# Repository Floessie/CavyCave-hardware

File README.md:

# CavyCave (hardware)

[![CC BY-SA 4.0][cc-by-sa-shield]][cc-by-sa]

## About

*CavyCave* is a temperature controlled box for guinea pigs and other small animals kept outside in winter. This repository holds the KiCad files for the controller board.

### The box

The box is built around a dark floor tile on a base frame of battens. Walls and top cover are made of 17&nbsp;mm thick, glued spruce floorboards. The front wall is fixed with four latches and can be removed for cleaning the interior. A number of load resistors fixed with thermal glue underneath the tile provide comfortable warmth to the top, helped by a polyurethane panel, which is clamped into the base frame at the bottom.

A hole in the top right corner of the box serves together with a fan as the exhaust air outlet. To protect the cavies from inspecting the fan too closely, a two-walled plywood housing is glued onto the backside of the box corner.

Two sensors monitor the temperature and humidity: a DHT22 for air temperature and humidity located in the top right corner of the box near the fan, and a cased DS18B20 under the tile for the floor temperature.

                       | 
-----------------------------------------------------|-------------------------------------------------
 | 

### The controller board

The heart and brain of the controller board is an ATmega328P-PU as found on the popular Arduino boards. Internally supplied with 3.3&nbsp;volts it connects two DHT22 temperature and humdity sensors and two DS18B20 temperature sensors as input and drives two heating circuits and one fan. The input voltage for the board, the fan, and the heating is 5&nbsp;volts. Depending on the load resistors the heating power is about 15 to 20&nbsp;watts.

The control system can be monitored, configured and remotely controlled by an nRF24L01+.

#### BOM

Quantity | Part | Mandatory
---------|------|----------
1 | Diode 1N5817 | :heavy_check_mark:
1 | Diode 1N4001 | :heavy_check_mark:
2 | Capacitor 22pF |
5 | Capacitor 100nF | :heavy_check_mark:
1 | Capacitor 100nF |
2 | Capacitor 1µF | :heavy_check_mark:
1 | Capacitor 10µF | :heavy_check_mark:
1 | Capacitor 10µF |
1 | Capacitor 100µF | :heavy_check_mark:
1 | Resistor 100Ω | :heavy_check_mark:
1 | Resistor 100Ω |
1 | Resistor 220Ω | :heavy_check_mark:
1 | Resistor 4.7kΩ | :heavy_check_mark:
1 | Resistor 4.7kΩ |
2 | Resistor 10kΩ | :heavy_check_mark:
1 | Resistor 10kΩ |
1 | Resistor 100kΩ | :heavy_check_mark:
1 | Resistor 100kΩ |
1-6 | Resistor for LED | :heavy_check_mark:
12-18 | Load resistor 22Ω VitrOhm KH208-810B22R | :heavy_check_mark:
2m+ | Silver plated copper wire 0.8mm | :heavy_check_mark:
1 | Bicolor (3 pin, CC) or RGB (4 pin, CC) LED | :heavy_check_mark:
1 | Transistor BC337-40 | :heavy_check_mark:
1 | LDO regulator MCP1702-3002 | :heavy_check_mark:
2 | Terminal block RND 205-00232 | :heavy_check_mark:
1 | Black 4mm socket Hirschmann 930 176-100 |
1 | Red 4mm socket Hirschmann 930 176-101 |
1 | MOSFET IRLIZ34N | :heavy_check_mark:
1 | MOSFET IRLIZ34N |
1 | Sensor DHT22 | :heavy_check_mark:
1 | Sensor DHT22 |
1 | Sensor DS18B20 | :heavy_check_mark:
1 | Sensor DS18B20 |
1 | Fan Sunon MB40100V2-000U-A99 | :heavy_check_mark:
1 | Crystal HC49U 8MHz |
1 | Pin socket 2x4 |
1 | IDC header 2x3 |
1 | Radio module nRF24L01+ |
x | Single row pin headers | :heavy_check_mark:

### History

This project started in the fall of 2018 with a large box for four cavies and two "rooms" ("vestibule" and "lounge") seperately heated. When one cavy was pushed out of the group in summer 2019 another smaller box had to be built, which has only one heating circuit. For the first box I experimented with 9V input to get 30&nbsp;watts heating power, but that was too much for the polyurethane panel and resulted in hot spots over the load resistors. Still, this could be a solution for even larger boxes with more and higher resistive load resistors as it's easier to find high power 9V supplies than 5V supplies. The fan must then be adjusted accordingly. The MCP1702-3002 LDO regulator for the internal 3.3&nbsp;volts supports up to 13.2&nbsp;volts input operating voltage.

The prototype circuit proved itself two winters, so now it was time to convert it to a real PCB.

## License

This work is licensed under a
[Creative Commons Attribution-ShareAlike 4.0 International License][cc-by-sa].

[![CC BY-SA 4.0][cc-by-sa-image]][cc-by-sa]

[cc-by-sa]: http://creativecommons.org/licenses/by-sa/4.0/
[cc-by-sa-image]: https://licensebuttons.net/l/by-sa/4.0/88x31.png
[cc-by-sa-shield]: https://img.shields.io/badge/License-CC%20BY--SA%204.0-lightgrey.svg

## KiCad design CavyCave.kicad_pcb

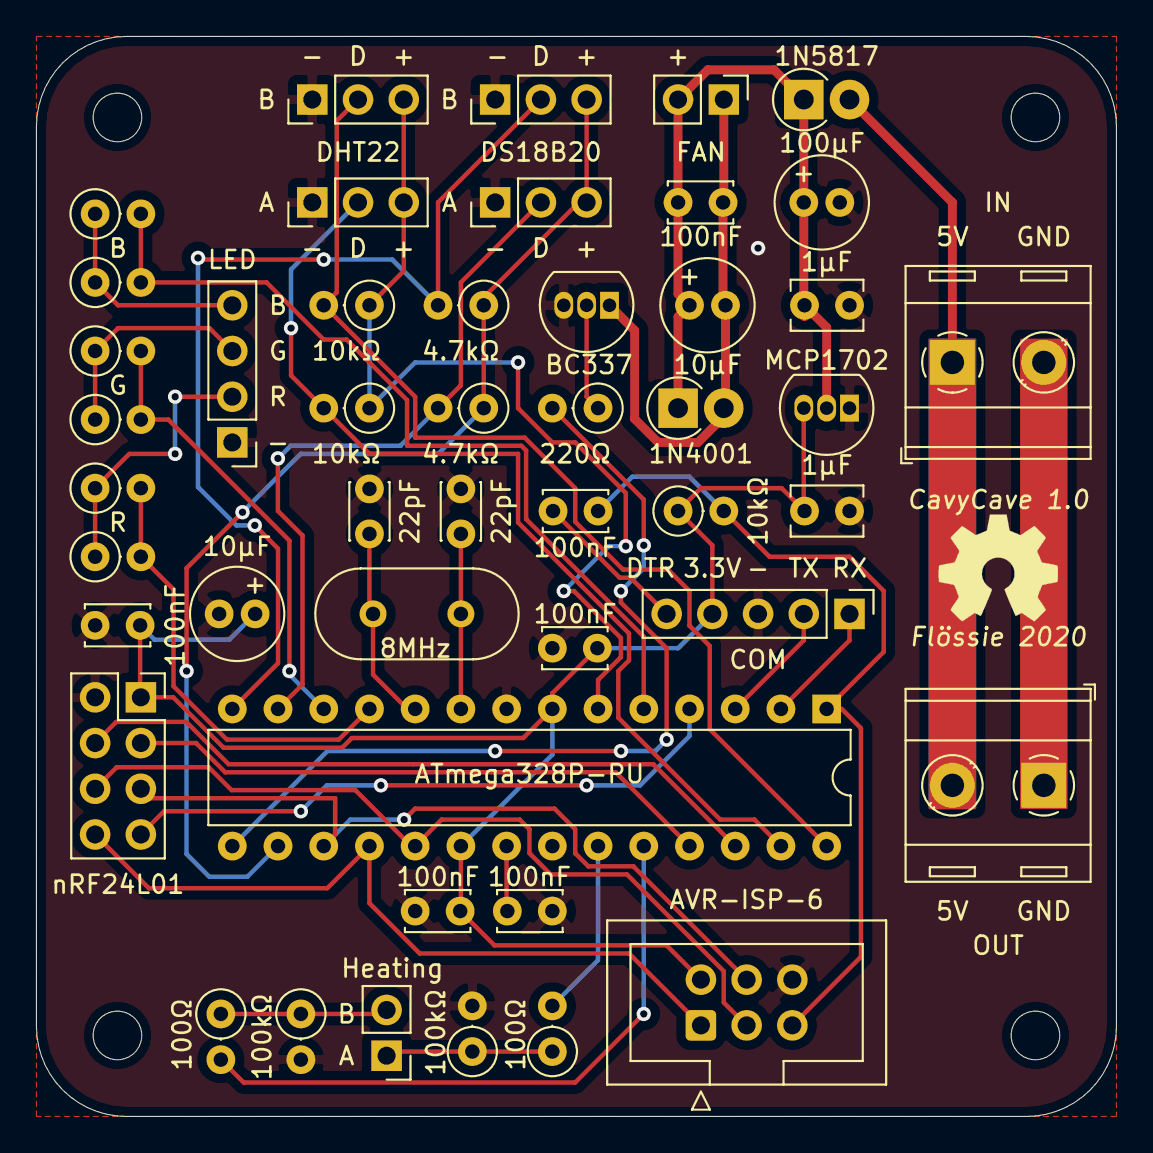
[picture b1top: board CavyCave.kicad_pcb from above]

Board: 2 copper layers, 60.0 x 60.0 mm, 47 parts (0 on the bottom side), 36 nets.

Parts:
B: R; R_Axial_DIN0207_L6.3mm_D2.5mm_P2.54mm_Vertical
C1, C2: 1µF; C_Disc_D3.8mm_W2.6mm_P2.50mm
C3: 100µF; C_Radial_D5.0mm_H11.0mm_P2.00mm
C4, C6, C7, C10, C12, C13: 100nF; C_Disc_D3.4mm_W2.1mm_P2.50mm
C5, C11: 10µF; C_Radial_D5.0mm_H11.0mm_P2.00mm
C8, C9: 22pF; C_Disc_D3.0mm_W2.0mm_P2.50mm
D1: 1N5817; D_DO-41_SOD81_P2.54mm_Vertical_AnodeUp
D2: 1N4001; D_DO-41_SOD81_P2.54mm_Vertical_AnodeUp
G: R; R_Axial_DIN0207_L6.3mm_D2.5mm_P2.54mm_Vertical
J1: IN; TerminalBlock_RND_205-00287_1x02_P5.08mm_Horizontal
J2: OUT; TerminalBlock_RND_205-00287_1x02_P5.08mm_Horizontal
J3: FAN; PinHeader_1x02_P2.54mm_Vertical
J4: LED; PinHeader_1x04_P2.54mm_Vertical
J5: Heating; PinHeader_1x02_P2.54mm_Vertical
J6: COM; PinHeader_1x05_P2.54mm_Vertical
J7: DHT22 A; PinHeader_1x03_P2.54mm_Vertical
J8: DHT22 B; PinHeader_1x03_P2.54mm_Vertical
J9: nRF24L01; PinSocket_2x04_P2.54mm_Vertical
J10: AVR-ISP-6; IDC-Header_2x03_P2.54mm_Vertical
J11: DS18B20 A; PinHeader_1x03_P2.54mm_Vertical
J12: DS18B20 B; PinHeader_1x03_P2.54mm_Vertical
Q1: BC337; TO-92_Inline
R, R4, R6, R8: R; R_Axial_DIN0207_L6.3mm_D2.5mm_P2.54mm_Vertical
R1: 220Ω; R_Axial_DIN0207_L6.3mm_D2.5mm_P2.54mm_Vertical
R2, R13, R14: 10kΩ; R_Axial_DIN0207_L6.3mm_D2.5mm_P2.54mm_Vertical
R9, R11: 100Ω; R_Axial_DIN0207_L6.3mm_D2.5mm_P2.54mm_Vertical
R10, R12: 100kΩ; R_Axial_DIN0207_L6.3mm_D2.5mm_P2.54mm_Vertical
R15, R16: 4.7kΩ; R_Axial_DIN0207_L6.3mm_D2.5mm_P2.54mm_Vertical
U1: MCP1700-3302; TO-92_Inline
U2: ATmega328P-PU; DIP-28_W7.62mm
Y1: 8MHz; Crystal_HC49-U_Vertical

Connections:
+3V3: C1.2, C4.2, C6.2, C11.1, C12.2, J6.4, J9.1, J10.2, R2.1, U1.3, U2.7, U2.20
/5V: C2.2, C3.1, C5.1, C7.1, D1.1, D2.1, J3.2, U1.2
/B: B.2, R8.2, U2.5
/CE: J9.4, U2.26
/CSN: J9.3, U2.25
/DHT_A: J7.2, R13.2, U2.27
/DHT_B: J8.2, R14.2, U2.28
/DHT_PWR: J7.3, J8.3, R13.1, R14.1, U2.6
/DS_A: J11.2, R15.2, U2.13
/DS_B: J12.2, R16.2, U2.14
/DS_PWR: J11.3, J12.3, R15.1, R16.1, U2.16
/FAN: R1.2, U2.15
/G: G.2, R6.2, U2.12
/HEAT_A: R9.2, U2.23
/HEAT_B: R11.2, U2.24
/IRQ: J9.7, U2.4
/MISO: J9.8, J10.1, U2.18
/MOSI: J9.5, J10.4, U2.17
/R: R.2, R4.2, U2.11
/RST: C10.1, J10.5, R2.2, U2.1
/RX: J6.1, U2.2
/SCK: J9.6, J10.3, U2.19
/TX: J6.2, U2.3
GND: C1.1, C2.1, C3.2, C4.1, C6.1, C8.2, C9.2, C11.2, C12.1, C13.1, J1.2, J2.1, J4.1, J6.3, J7.1, J8.1, J9.2, J10.6, J11.1, J12.1, Q1.3, R10.2, R12.2, U1.1, U2.8, U2.22
unnamed: C5.2, C7.2, D2.2, J3.1, Q1.1
unnamed: C8.1, U2.10, Y1.2
unnamed: C9.1, U2.9, Y1.1
unnamed: C10.2, J6.5
unnamed: C13.2, U2.21
unnamed: D1.2, J1.1, J2.2
unnamed: J4.2, R.1, R4.1
unnamed: G.1, J4.3, R6.1
unnamed: B.1, J4.4, R8.1
unnamed: J5.1, R9.1, R10.1
unnamed: J5.2, R11.1, R12.1
unnamed: Q1.2, R1.1

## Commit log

2020-11-29 Add v1.0 KiCad files, license, and minimal README
2020-12-01 Roughly describe the box and the controller board
2020-12-01 Fix some typos
2020-12-01 Add some pictures of the boxes
2020-12-01 Formatting
2020-12-01 Add BOM
2020-12-01 Add LED to BOM
2020-12-02 Add load resistors and wire to BOM
2020-12-04 Add input sockets
